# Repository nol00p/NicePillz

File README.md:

# NicePillz
this is a pillzmod pcb reworked to be dedicated to the nice!nano

Changes include:
- moved the register to the high frequency pins
- Terminal blocks for easy install of the battery and power switch
- moved col0 directly to the nice!nano so the keyboard can wake up by pressing the top ESC key.

## Bill of materials

| Position          | Description      | Qty | Notes                                      |
| ----------------- | ---------------- | --- | ------------------------------------------ |
| J1–J8             | Molex 39-53-2135 | 6   | [Mouser](https://eu.mouser.com/ProductDetail/Molex/39-53-2135?qs=cm0cgiBciNYI3jeMaEn0Ng%3D%3D) |
|                   | LED              | 2   | [Amazon](https://www.amazon.fr/dp/B005Q2MZ4Q) |
| ble-pwr             | 10k resistor     | 2   | Affects LED brightness. Smaller = brighter |
| U2                | 74HC595          | 1   | [Amazon](https://www.amazon.fr/dp/B093Y2MQGV) |
| U2                | 16-pin IC socket | 1   | [Amazon](https://www.amazon.fr/dp/B07ZCRTRXK?ref=ppx_yo2ov_dt_b_fed_asin_title&th=1) |
|                   | Terminals        | 3   | [AliExpress](https://fr.aliexpress.com/item/1005006589335718.html)  |
|                   | reset button     | 1   | [AliExpress](https://fr.aliexpress.com/item/1005007623070623.html)  |
|                   | Power button     | 1   | [Amazon](https://www.amazon.fr/dp/B08L484J7W) |
|                   | Nice!Nano        | 1   |                                            |
|                   | 3.7V battery - 2000mAh | 1   | [Amazon](https://www.amazon.fr/dp/B08214DJLJ) |
|                   | USB-C panel mount| 1   | [AliExpress](https://fr.aliexpress.com/item/1005009401577622.html)                        |

## Assembly
Assembly is very straight forward

LED: the trickiest part might be the LED, make sure to first drop them on the chassi pockets and solder them when in place. 
note the short leg goes to the square pad. 

terminal: when installing the terminal make sure they are facing outward so the little arrow indicated the positive wire. 

## ZMK
see: https://github.com/nol00p/ZMK-NicePillz

## Attribution
This project is a fork of https://github.com/dcpedit/pillzmod

## Thumbcluster
Next the Thumbcluster, the plan here is to use the same terminal to be able to reuse the ribbon cables. and include hot swap sockets. Get in touch if that is something of interest.

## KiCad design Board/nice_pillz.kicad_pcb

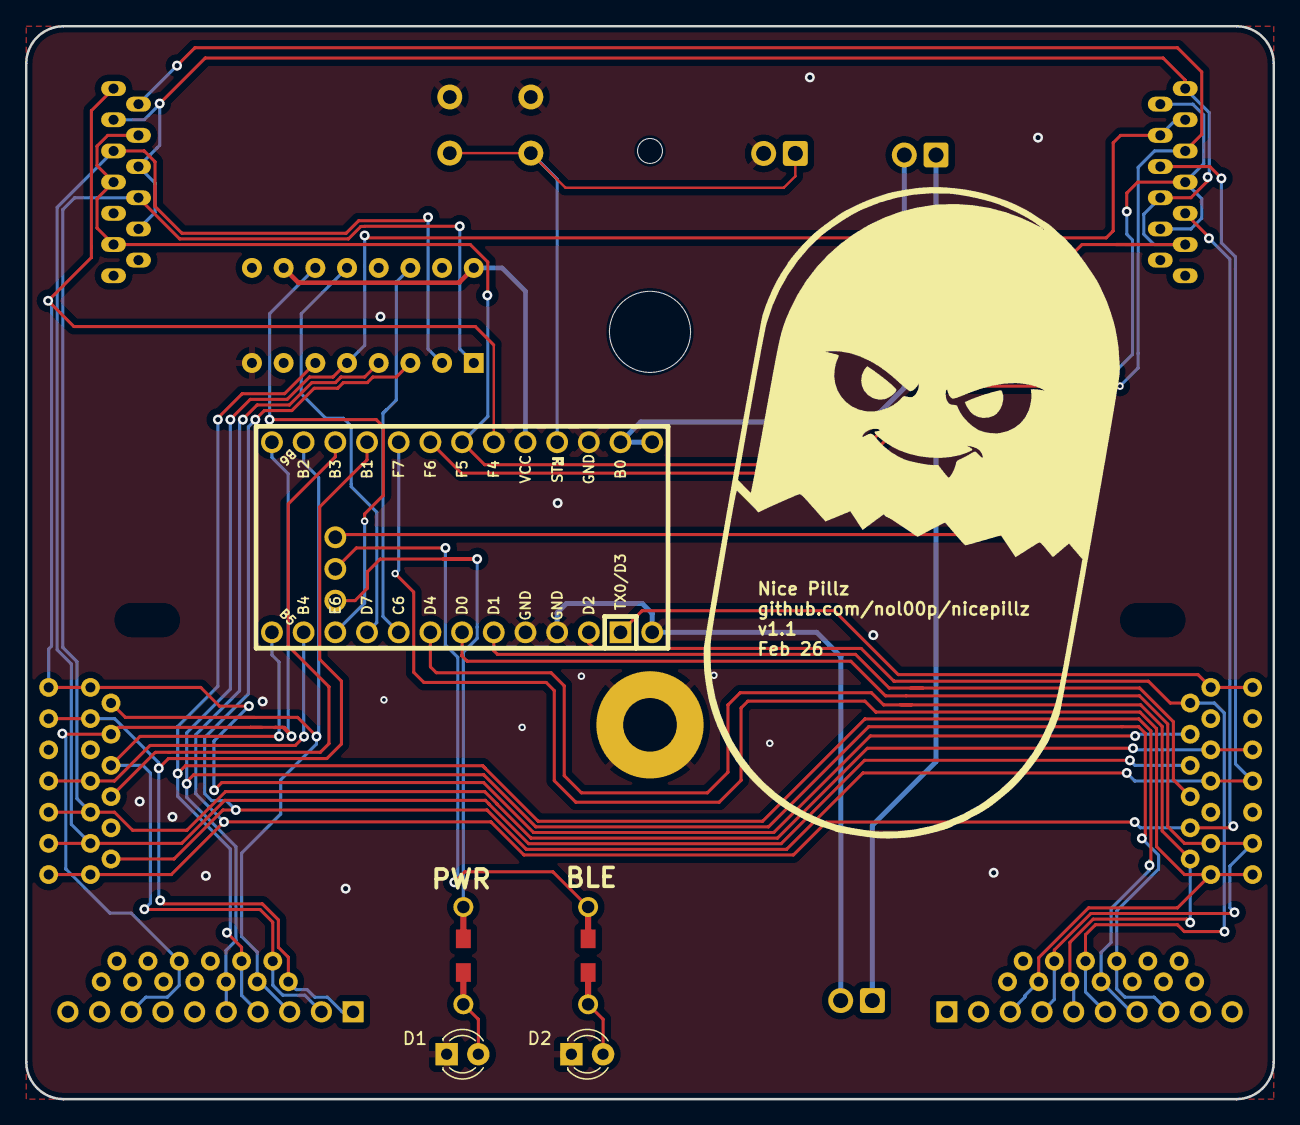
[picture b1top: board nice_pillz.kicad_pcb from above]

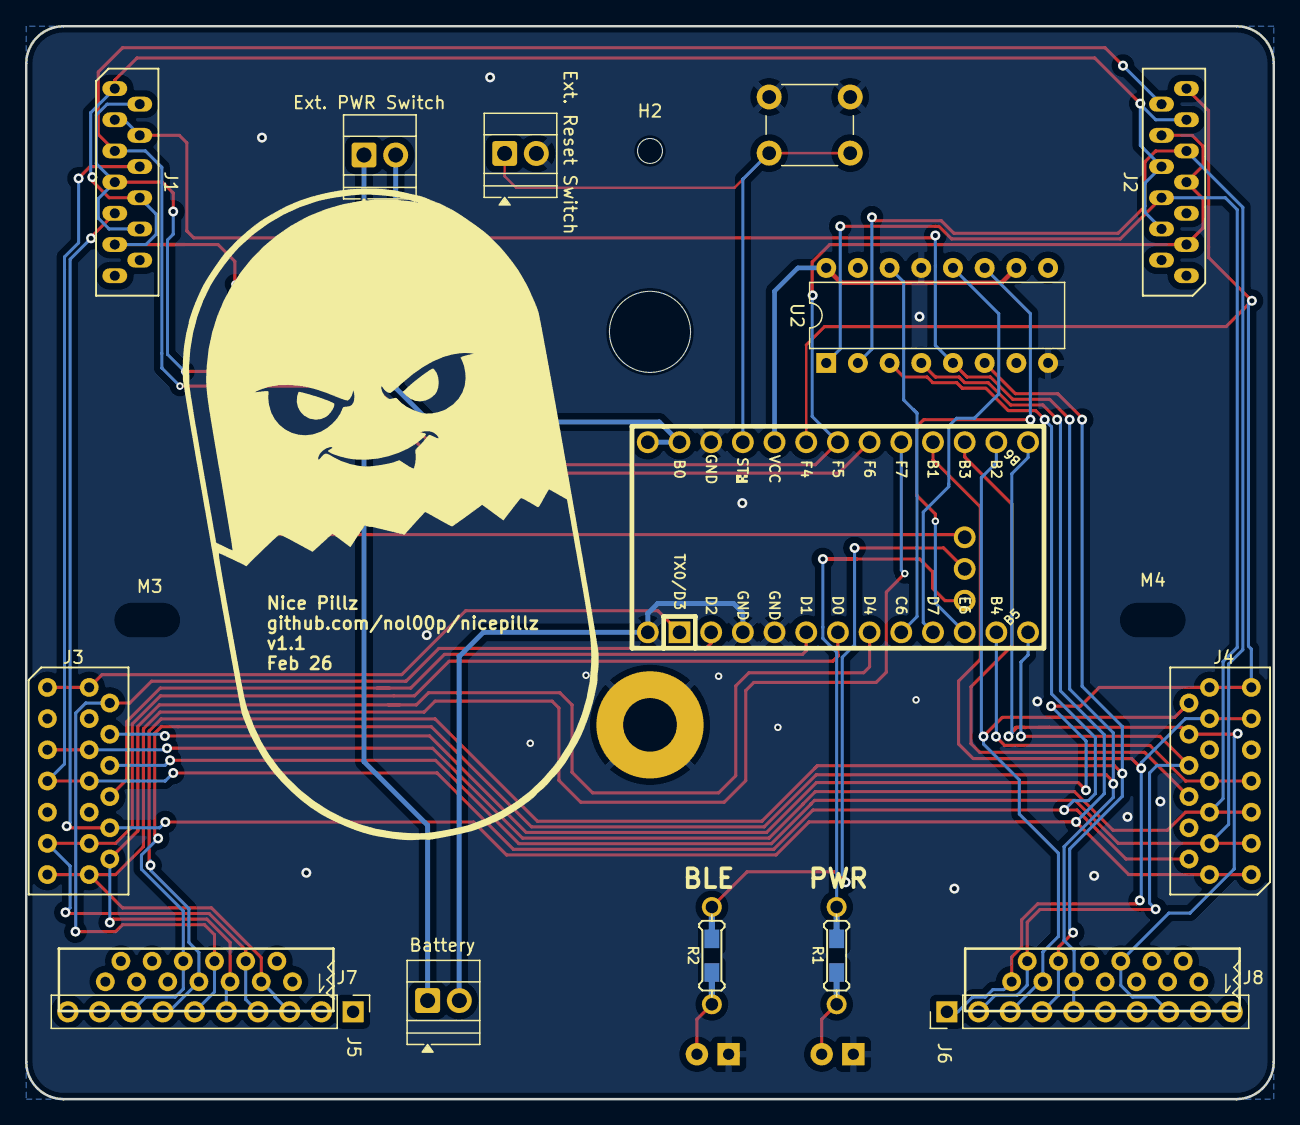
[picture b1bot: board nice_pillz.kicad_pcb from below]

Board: 2 copper layers, 100.0 x 86.0 mm, 22 parts (19 on the bottom side), 34 nets.

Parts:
Battery: TerminalBlock_Xinya_XY308-2.54-2P_1x02_P2.54mm_Ho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; TerminalBlock_Xinya_XY308-2.54-2P_1x02_P2.54mm_Horizontal
D1: LED_CAPS; LED_D3.0mm
D2: LED_NUM; LED_D3.0mm
Ext. PWR Switch, Ext. Reset Switch: TerminalBlock_Xinya_XY308-2.54-2P_1x02_P2.54mm_Ho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; TerminalBlock_Xinya_XY308-2.54-2P_1x02_P2.54mm_Horizontal
H1: mounting pad; MountingHole_4.3mm_M4_Pad
H2: mounting pad; MountingHole_2mm
J1, J2: Conn_01x13; Molex_0039532135
J3, J4: Conn_01x13; Molex_039532134
J5, J6: Conn_01x10; Pin_Header_Straight_1x10_Pitch2.54mm
J7, J8: Conn_01x13; 39-53-2135
M1: MountingHole_6.4mm_M6
M3, M4: MountingHole_4.3mm_M4
R1, R2: R_US; Resistor-Hybrid
U1: nice!nanov2; nice_nano_v2
U2: 74HC595; DIP-16_W7.62mm

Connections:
+5V: U1.21 (VCC), U2.10 (~SRCLR), U2.16 (VCC)
/COL_0: J2.13, J3.4, J4.13, U1.20 (A3/PF4)
/COL_1: J2.6, J3.5, J4.5, U2.1 (QB)
/COL_2: J2.9, J3.6, J4.3, U2.2 (QC)
/COL_3: J1.6, J3.7, J4.2, U2.3 (QD)
/COL_4: J1.9, J3.10, J4.1, U2.4 (QE)
/COL_5: J1.3, J1.4, J5.8, J6.5, J7.8, J8.9, U2.5 (QF)
/COL_6: J5.7, J6.4, J7.7, J8.10, U2.6 (QG)
/LATCH: U1.9 (6/PD7), U2.12 (RCLK)
/LED_CAPS_LOCK: R1.2, U1.26 (D5)
/LED_NUM_LOCK: R2.2, U1.27 (C7)
/RESET: Ext. Reset Switch.1, U1.22 (RST)
/ROW_0: J4.6, U1.15 (14/PB3)
/ROW_1: J4.7, U1.11 (8/PB4)
/ROW_2: J4.8, J6.2, J8.12, U1.12 (9/PB5)
/ROW_3: J4.10, J6.8, J8.6, U1.13 (10/PB6)
/ROW_4: J4.11, J6.1, J8.13, U1.16 (15/PB1)
/ROW_5: J4.12, J6.3, J8.11, U1.14 (16/PB2)
/ROW_6: J3.13, J5.3, J7.3, U1.17 (A0/PF7)
/ROW_7: J3.11, J5.4, J7.4, U1.6 (3/PD0)
/ROW_8: J3.12, J5.5, J7.5, U1.7 (4/PD4)
/ROW_9: J3.2, J5.6, J7.6, U1.2 (RX1/PD2)
/ROW_10: J3.1, U1.1 (TX0/PD3)
/ROW_11: J3.8, U1.5 (2/PD1)
/ROW_12: J1.5, J2.12, U1.18 (A1/PF6)
/ROW_13: J1.1, J1.8, J1.11, J2.4, J2.8, J2.11, U1.28 (F1)
/ROW_14: J1.2, J1.7, J1.10, J2.3, J2.7, J2.10, U1.19 (A2/PF5)
/SPI_MOSI: U1.8 (5/PC6), U2.14 (SER)
/SPI_SCK: U1.10 (7/PE6), U2.11 (SRCLK)
BAT: Ext. PWR Switch.2, U1.24 (B0)
BAT+: Battery.1, Ext. PWR Switch.1
GND: D1.1 (K), D2.1 (K), Ext. Reset Switch.2, H1.1, U1.3 (GND), U1.4 (GND), U1.23 (GND), U2.8 (GND), U2.13 (~OE)
unnamed: D1.2 (A), R1.1
unnamed: D2.2 (A), R2.1

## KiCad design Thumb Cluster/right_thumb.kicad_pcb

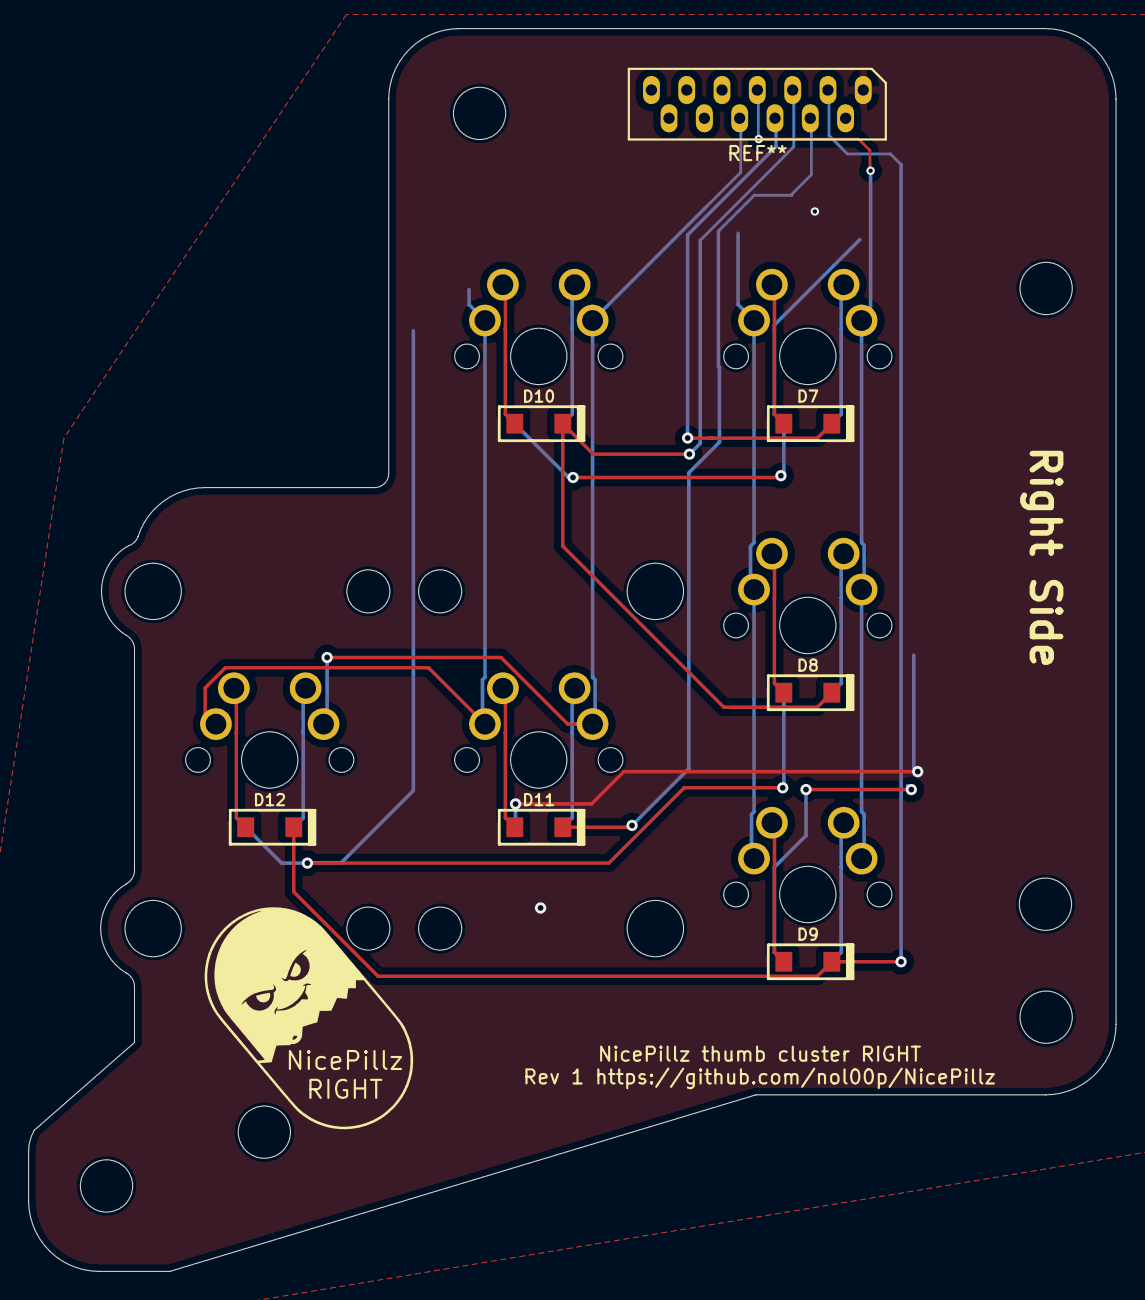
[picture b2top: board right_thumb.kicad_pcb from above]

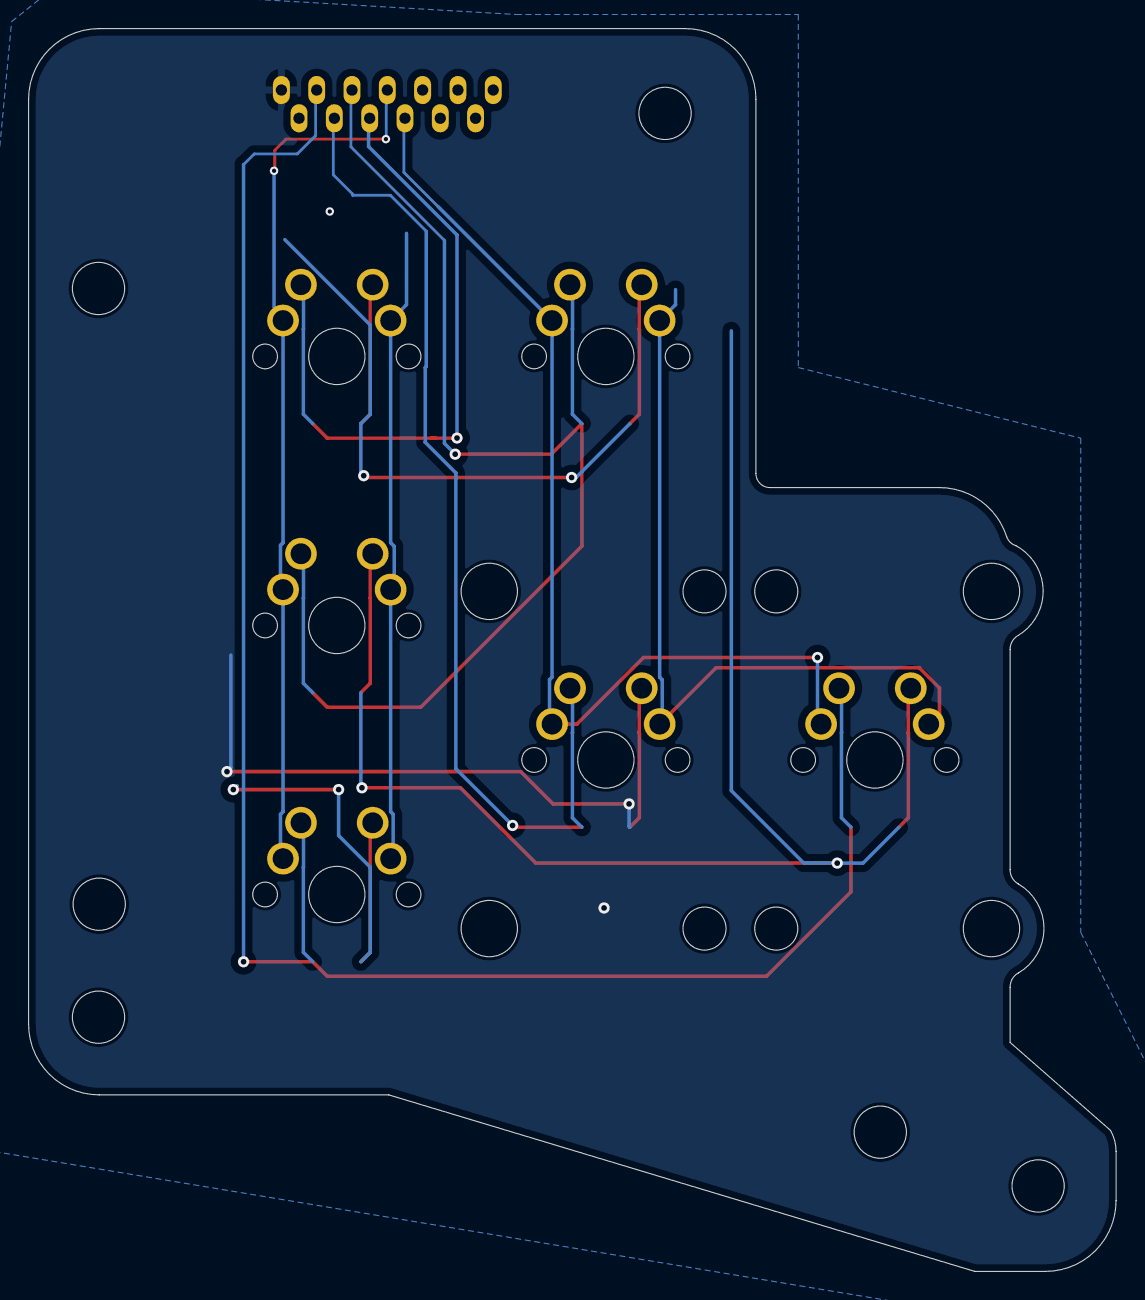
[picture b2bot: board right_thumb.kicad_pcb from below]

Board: 2 copper layers, 77.0 x 88.0 mm, 24 parts (6 on the bottom side), 12 nets.

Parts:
D7, D8, D9, D10, D11, D12: D; D_SOD123W_hand
MX25, MX35, MX55, MX56: MX-NoLED; MXOnly-1U-NoLED-twin
MX36, MX46: MX-NoLED; MXOnly-2U-VerticalStabilizers-NoLED-twin
MX65: MX-NoLED; MXOnly-2U-VerticalStabilizers-NoLED
MX66, MX85, MX86, MX96: MX-NoLED; MXOnly-1U-NoLED
MX75: MX-NoLED; MXOnly-2U-ReversedVerticalStabilizers-NoLED
REF1, REF2, REF3, REF4, REF5, REF6: MountingHole_3.7mm

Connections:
/COL_L5: MX25.1 (COL), MX35.1 (COL), MX55.1 (COL)
/COL_L6: MX36.1 (COL), MX46.1 (COL), MX56.1 (COL)
/COL_R5: MX65.1 (COL), MX75.1 (COL), MX85.1 (COL)
/COL_R6: MX66.1 (COL), MX86.1 (COL), MX96.1 (COL)
/ROW_6: D9.1 (K), D12.1 (K)
/ROW_8: D8.1 (K), D10.1 (K)
unnamed: D7.2 (A), MX96.2 (ROW)
unnamed: D8.2 (A), MX86.2 (ROW)
unnamed: D9.2 (A), MX66.2 (ROW)
unnamed: D10.2 (A), MX85.2 (ROW)
unnamed: D11.2 (A), MX75.2 (ROW)
unnamed: D12.2 (A), MX65.2 (ROW)

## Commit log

2026-02-14 git init
2026-02-14 Project description
2026-02-16 full update
2026-02-16 update 3d
2026-02-16 battery connection
2026-02-20 Production files created
2026-02-23 folder structure and firmware
2026-02-23 v1.1 new pcb and overlay config
2026-02-24 note update
2026-03-16 firmware upadate
2026-03-17 documenation update
2026-03-17 clean up
2026-03-18 updated BOM
